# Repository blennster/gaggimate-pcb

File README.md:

This is a reimplemenation of the gaggimate PCB. It is not officaly supported and never will be.

This work is in no way affiliated with the https://gaggimate.eu/ project.

## License

This work is licensed under CC BY-NC-SA 4.0. To view a copy of this license, visit https://creativecommons.org/licenses/by-nc-sa/4.0/

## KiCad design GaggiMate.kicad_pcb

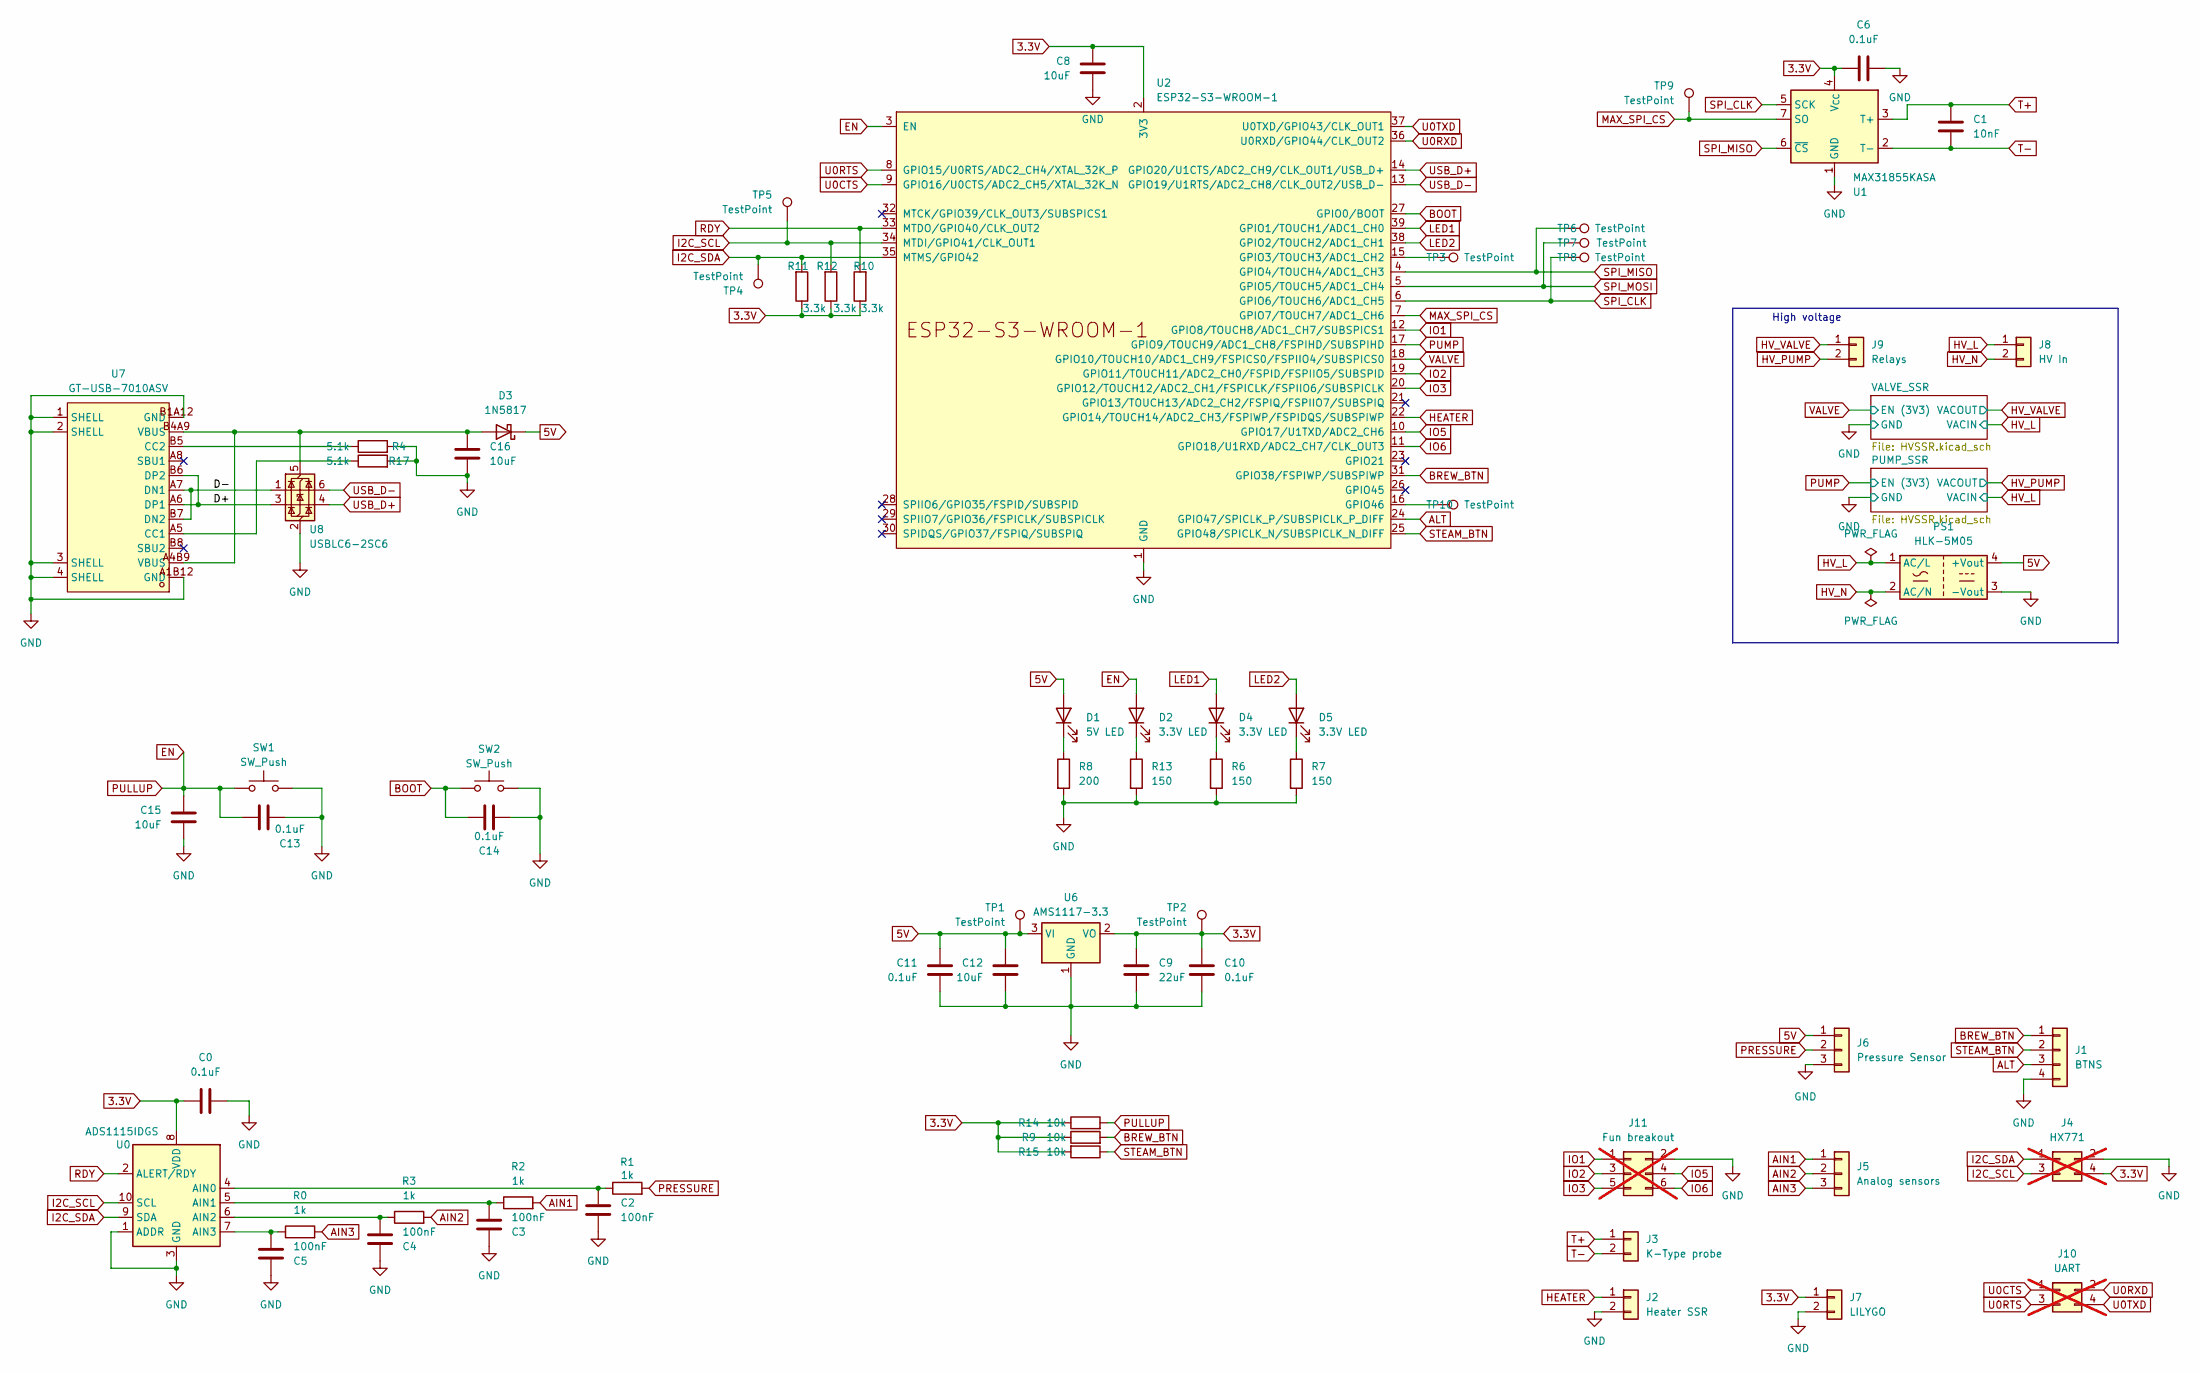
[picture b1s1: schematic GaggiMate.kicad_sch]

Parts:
C0, C6, C10, C11, C13, C14: 0.1uF; C_0603_1608Metric
C1: 10nF; C_0603_1608Metric
C2, C3, C4, C5: 100nF; C_0603_1608Metric
C8, C12, C15, C16: 10uF; C_0603_1608Metric
C9: 22uF; C_0603_1608Metric
D1: 5V LED; LED_0603_1608Metric
D2, D4, D5: 3.3V LED; LED_0603_1608Metric
D3: 1N5817; D_SOD-123
J1: BTNS; JST_PH_B4B-PH-K_1x04_P2.00mm_Vertical
J2: Heater SSR; JST_PH_B2B-PH-K_1x02_P2.00mm_Vertical
J3: K-Type probe; CONN-TH_2P-P2.54_DIBO_DB141V-2.54-2P
J4: HX771; PinHeader_2x02_P2.54mm_Vertical_SMD; not fitted
J5: Analog sensors; CONN-TH_3P-P2.54_DIBO_DB141V-2.54-3P
J6: Pressure Sensor; CONN-TH_3P-P2.54_DIBO_DB141V-2.54-3P
J7: LILYGO; JST_PH_B2B-PH-K_1x02_P2.00mm_Vertical
J8: HV In; CONN-TH_2P-P5.08_DIBO_DB142V-5.08-2P
J9: Relays; CONN-TH_2P-P5.08_DIBO_DB142V-5.08-2P
J10: UART; PinHeader_2x02_P2.54mm_Vertical_SMD; not fitted
J11: Fun breakout; PinHeader_2x03_P2.54mm_Vertical_SMD; not fitted
PS1: HLK-5M05; Converter_ACDC_Hi-Link_HLK-5Mxx
R0, R1, R2, R3: 1k; R_0603_1608Metric
R4, R17: 5.1k; R_0603_1608Metric
R6, R7, R13: 150; R_0603_1608Metric
R8: 200; R_0603_1608Metric
R9, R14, R15: 10k; R_0603_1608Metric
R10, R11, R12: 3.3k; R_0603_1608Metric
SW1, SW2: SW_Push; SW_SPST_TL3342
TP1, TP2, TP3, TP4, TP5, TP6, TP7, TP8, TP9, TP10: TestPoint; TestPoint_Pad_D1.0mm
U0: ADS1115IDGS; TSSOP-10_3x3mm_P0.5mm
U1: MAX31855KASA; SOIC-8_3.9x4.9mm_P1.27mm
U2: ESP32-S3-WROOM-1; WIRELM-SMD_ESP32-S3-WROOM-1
U6: AMS1117-3.3; SOT-223-3_TabPin2
U7: GT-USB-7010ASV; USB-C-SMD_G-SWITCH_GT-USB-7010ASV; LCSC Part C2988369
U8: USBLC6-2SC6; SOT-23-6

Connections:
3.3V: C0.1, C6.1, C8.2, C9.1, C10.1, J4.4, J7.1, R9.1, R10.1, R11.1, R12.1, R14.1, R15.2, TP2.1, U0.8 (VDD), U1.4 (V_{CC}), U2.2 (3V3), U6.2 (VO)
5V: C11.2, C12.1, D1.2 (A), D3.1 (K), J6.1, PS1.4 (+Vout), TP1.1, U6.3 (VI)
/D+: U7.A6 (DP1), U7.B6 (DP2), U8.3 (I/O2)
/D-: U7.A7 (DN1), U7.B7 (DN2), U8.1 (I/O1)
AIN1: J5.1, R2.2
AIN2: J5.2, R3.2
AIN3: J5.3, R0.2
ALT: J1.3, U2.24 (GPIO47/SPICLK_P/SUBSPICLK_P_DIFF)
BOOT: C14.1, SW2.1, U2.27 (GPIO0/BOOT)
BREW_BTN: J1.1, R9.2, U2.31 (GPIO38/FSPIWP/SUBSPIWP)
EN: C13.1, C15.1, D2.2 (A), R14.2, SW1.1, U2.3 (EN)
GND: C0.2, C2.2, C3.1, C4.1, C5.1, C6.2, C8.1, C9.2, C10.2, C11.1, C12.2, C13.2, C14.2, C15.2, C16.2, J1.4, J2.2, J4.2, J6.3, J7.2, J11.2, PS1.3 (-Vout), R4.2, R6.2, R7.2, R8.2, R13.2, R17.2, SW1.2, SW2.2, U0.1 (ADDR), U0.3 (GND), U1.1 (GND), U2.1 (GND), U2.40 (GND), U2.41 (GND), U6.1 (GND), U7.1 (SHELL), U7.2 (SHELL), U7.3 (SHELL), U7.4 (SHELL), U7.A1B12 (GND), U7.B1A12 (GND), U8.2 (GND); also elsewhere on the board
HEATER: J2.1, U2.22 (GPIO14/TOUCH14/ADC2_CH3/FSPIWP/FSPIDQS/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)
HV_L: J8.1, PS1.1 (AC/L); also elsewhere on the board
HV_N: J8.2, PS1.2 (AC/N)
HV_PUMP: J9.2; also elsewhere on the board
HV_VALVE: J9.1; also elsewhere on the board
I2C_SCL: J4.3, R12.2, TP5.1, U0.10 (SCL), U2.34 (MTDI/GPIO41/CLK_OUT1)
I2C_SDA: J4.1, R11.2, TP4.1, U0.9 (SDA), U2.35 (MTMS/GPIO42)
IO1: J11.1, U2.12 (GPIO8/TOUCH8/ADC1_CH7/SUBSPICS1)
IO2: J11.3, U2.19 (GPIO11/TOUCH11/ADC2_CH0/FSPID/FSPIIO5/S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)
IO3: J11.5, U2.20 (GPIO12/TOUCH12/ADC2_CH1/FSPICLK/FSPIIO6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)
IO5: J11.4, U2.10 (GPIO17/U1TXD/ADC2_CH6)
IO6: J11.6, U2.11 (GPIO18/U1RXD/ADC2_CH7/CLK_OUT3)
LED1: D4.2 (A), U2.39 (GPIO1/TOUCH1/ADC1_CH0)
LED2: D5.2 (A), U2.38 (GPIO2/TOUCH2/ADC1_CH1)
MAX_SPI_CS: TP9.1, U1.7 (SO), U2.7 (GPIO7/TOUCH7/ADC1_CH6)
unnamed: D1.1 (K), R8.1
unnamed: D2.1 (K), R13.1
unnamed: C16.1, D3.2 (A), U7.A4B9 (VBUS), U7.B4A9 (VBUS), U8.5 (VBUS)
unnamed: D4.1 (K), R6.1
unnamed: D5.1 (K), R7.1
unnamed: C2.1, R1.1, U0.4 (AIN0)
unnamed: C3.2, R2.1, U0.5 (AIN1)
unnamed: C4.2, R3.1, U0.6 (AIN2)
unnamed: C5.2, R0.1, U0.7 (AIN3)
unnamed: TP3.1, U2.15 (GPIO3/TOUCH3/ADC1_CH2)
unnamed: TP10.1, U2.16 (GPIO46)
unnamed: R17.1, U7.A5 (CC1)
unnamed: R4.1, U7.B5 (CC2)
PRESSURE: J6.2, R1.2
PUMP: U2.17 (GPIO9/TOUCH9/ADC1_CH8/FSPIHD/SUBSPIHD); also elsewhere on the board
RDY: R10.2, U0.2 (ALERT/RDY), U2.33 (MTDO/GPIO40/CLK_OUT2)
SPI_CLK: TP8.1, U1.5 (SCK), U2.6 (GPIO6/TOUCH6/ADC1_CH5)
SPI_MISO: TP6.1, U1.6 (~CS), U2.4 (GPIO4/TOUCH4/ADC1_CH3)
SPI_MOSI: TP7.1, U2.5 (GPIO5/TOUCH5/ADC1_CH4)
STEAM_BTN: J1.2, R15.1, U2.25 (GPIO48/SPICLK_N/SUBSPICLK_N_DIFF)
T+: C1.1, J3.1, U1.3 (T+)
T-: C1.2, J3.2, U1.2 (T-)
U0CTS: J10.1, U2.9 (GPIO16/U0CTS/ADC2_CH5/XTAL_32K_N)
U0RTS: J10.3, U2.8 (GPIO15/U0RTS/ADC2_CH4/XTAL_32K_P)
U0RXD: J10.2, U2.36 (U0RXD/GPIO44/CLK_OUT2)
U0TXD: J10.4, U2.37 (U0TXD/GPIO43/CLK_OUT1)
USB_D+: U2.14 (GPIO20/U1CTS/ADC2_CH9/CLK_OUT1/USB_D+), U8.4 (I/O2)
USB_D-: U2.13 (GPIO19/U1RTS/ADC2_CH8/CLK_OUT2/USB_D-), U8.6 (I/O1)
VALVE: U2.18 (GPIO10/TOUCH10/ADC1_CH9/FSPICS0/FSPIIO4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); also elsewhere on the board

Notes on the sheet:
High voltage

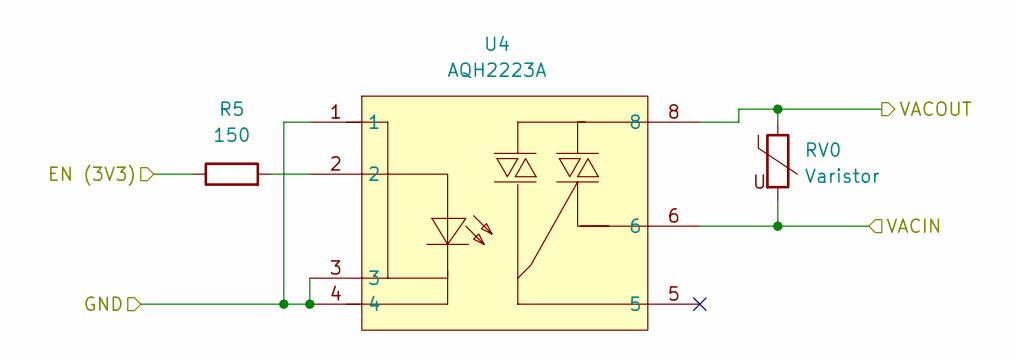
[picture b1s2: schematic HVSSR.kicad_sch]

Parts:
R5: 150; R_0603_1608Metric
RV0: Varistor; RES-SMD_L6.8-W5.9-LS7.8
U4: AQH2223A; SMD-8_7P-L9.8-W6.4-P2.54-BL-PE7; LCSC Part C153026

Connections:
GND: U4.1, U4.3, U4.4; also elsewhere on the board
HV_L: RV0.2, U4.6; also elsewhere on the board
HV_VALVE: RV0.1, U4.8; also elsewhere on the board
unnamed: R5.2, U4.2
VALVE: R5.1; also elsewhere on the board

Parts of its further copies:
R16: 150; R_0603_1608Metric
RV1: Varistor; RES-SMD_L6.8-W5.9-LS7.8
U9: AQH2223A; SMD-8_7P-L9.8-W6.4-P2.54-BL-PE7; LCSC Part C153026

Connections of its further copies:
GND: U9.1, U9.3, U9.4; also elsewhere on the board
HV_L: RV1.2, U9.6; also elsewhere on the board
HV_PUMP: RV1.1, U9.8; also elsewhere on the board
unnamed: R16.2, U9.2
PUMP: R16.1; also elsewhere on the board

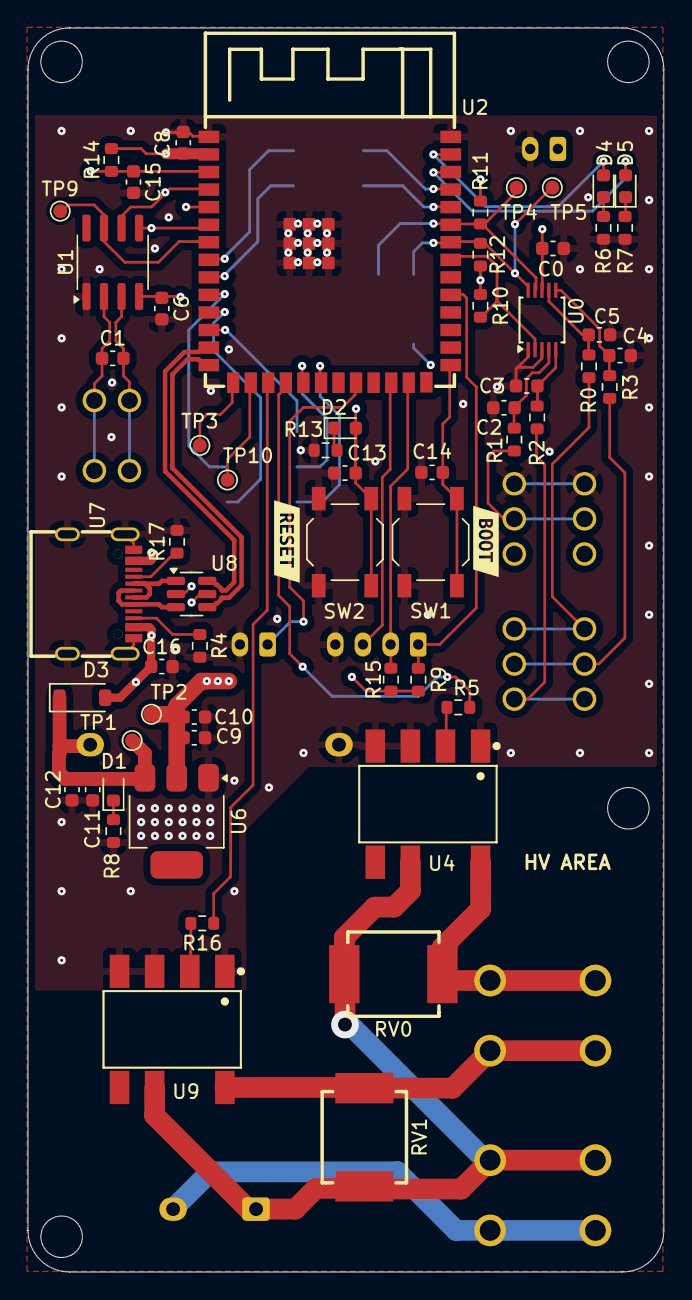
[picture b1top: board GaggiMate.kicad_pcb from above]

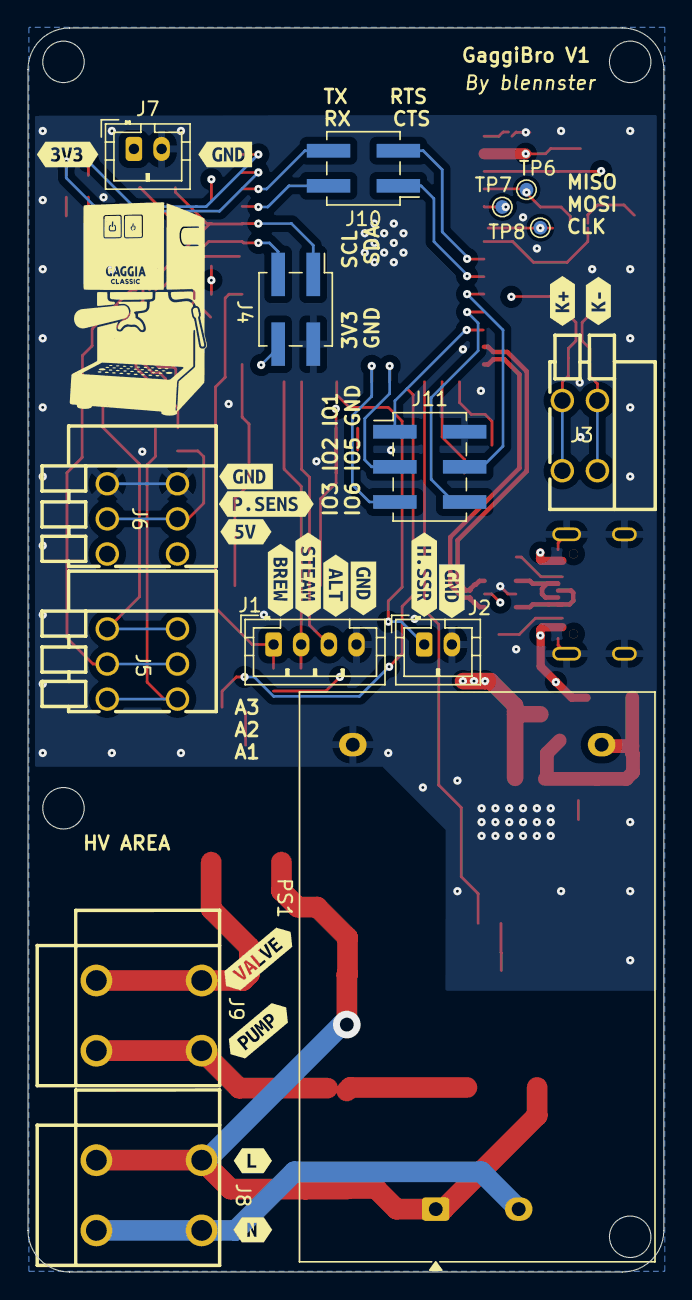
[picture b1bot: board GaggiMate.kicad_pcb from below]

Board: 4 copper layers, 46.0 x 90.0 mm, 92 parts (32 on the bottom side), 58 nets.

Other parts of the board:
kibuzzard-68D85A7C: G***; kibuzzard-68D85A7C
kibuzzard-68D85A63: G***; kibuzzard-68D85A63
kibuzzard-68D85AF0: G***; kibuzzard-68D85AF0
kibuzzard-68D85B00: G***; kibuzzard-68D85B00
kibuzzard-68D853DB, kibuzzard-68D853DB#2: G***; kibuzzard-68D853DB
kibuzzard-68D858A7: G***; kibuzzard-68D858A7
kibuzzard-68D858C6: G***; kibuzzard-68D858C6
kibuzzard-68D859D6: G***; kibuzzard-68D859D6
kibuzzard-68D8588D: G***; kibuzzard-68D8588D
kibuzzard-68D8589E: G***; kibuzzard-68D8589E
kibuzzard-68D8595E: G***; kibuzzard-68D8595E
kibuzzard-68D85755: G***; kibuzzard-68D85755
kibuzzard-68D85864: G***; kibuzzard-68D85864
kibuzzard-68D85872: G***; kibuzzard-68D85872
kibuzzard-68D85884: G***; kibuzzard-68D85884
kibuzzard-68D85899: G***; kibuzzard-68D85899
kibuzzard-68D85940: G***; kibuzzard-68D85940
kibuzzard-68D85954: G***; kibuzzard-68D85954

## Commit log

2025-09-18 inital commit
2025-09-18 updated power and began 5-3v regulator
2025-09-19 bunch of updates
    added:
    - relays
    - barrel jack
    - more proper routing
2025-09-20 attempt a HV stepdown and some PCB stuff
2025-09-20 remove ignored file
2025-09-20 update footprints, add 230v module, use SSRs and do some basic layouting
2025-09-21 update some footprints etc
2025-09-22 Moved front side components to other board, finished cap and resistor selection and maybe finalizing layout
2025-09-22 geographical referencing instead
2025-09-22 attempt some routing
2025-09-23 update analog filters and started some HV traces
2025-09-23 more routing and and programming buttons
2025-09-24 update layout a lot
2025-09-24 finalize layout and tracks?
2025-09-27 some updates
2025-09-27 release candidate 1
2025-09-27 add custom silkscreen and missing lilygo out pins
2025-09-27 make ready for release
2025-09-28 update to new footprint ad make stuff nice
2025-09-29 add missing models and finalize pcb
2025-09-29 released version
2025-09-30 Swap GND and 5V as they were mislabled
2025-10-25 update license
